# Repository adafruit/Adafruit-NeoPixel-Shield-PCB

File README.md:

## Adafruit NeoPixel Shield for Arduino - 40 RGB LED Pixel Matrix PCB

<a href="http://www.adafruit.com/products/1430"><br/>
Click here to purchase one from the Adafruit shop</a>

PCB files for the Adafruit NeoPixel Shield for Arduino - 40 RGB LED Pixel Matrix. Format is EagleCAD schematic and board layout
* https://www.adafruit.com/product/1430

### Description

Put on your sunglasses before putting this shield onto your 'duino - 40 eye-blistering RGB LEDs adorn the NeoPixel shield for a blast of configurable color. Arranged in a 5x8 matrix, each pixel is individually addressable. Only one pin (Digital #6) is required to control all the LEDs. You can cut a trace and use nearly any other pin if you need some customization.

To make it easy to start, the LEDs are by default powered from the 5V onboard Arduino supply. As long as you aren't lighting up all the pixels full power white that should be fine. If you want to power the shield with an external power supply, solder in the included terminal block (pro-tip: put it on the bottom of the board so it doesn't stick up) to wire in an external 4-6VDC power supply - that power supply will also power the Arduino and shield. If you want to use the terminal block to power the shield but keep the Arduino itself on DC or USB power only, cut the center of the solder jumper to the right of the terminal block. There's a polarity protection FET on the external input in case you wire the power backwards (we would never do that, it was, umm, a friend of ours, yeah that's it!)

If, say, you need MORE blinky, you can chain these together. For the second shield, connect the DIN connection to the first shield's DOUT. Also connect a ground pin together and power with 5V. There you go! You can chain as many as you'd like although after 5 or more shields you may run low on RAM if you're using an UNO.

We include both stacking headers and plain headers. Use whichever you prefer - there isn't a lot of space left over for the 'duino pin breakouts so if you want to wire up some other outputs or sensors the stacking headers are good. For a slim sturdy look, solder on the plain headers.

[Our detailed NeoPixel Uberguide has everything you need to use NeoPixels in any shape and size. Including ready-to-go library & example code for the Arduino UNO/Duemilanove/Diecimila, Flora/Micro/Leonardo, Trinket/Gemma, Arduino Due & Arduino Mega/ADK (all versions)](http://learn.adafruit.com/adafruit-neopixel-uberguide)

**Note**: The terminal blocks included with your product may be blue or black.

### License

Adafruit invests time and resources providing this open source design, please support Adafruit and open-source hardware by purchasing products from [Adafruit](https://www.adafruit.com)!

Designed by Limor Fried/Ladyada for Adafruit Industries.

Creative Commons Attribution/Share-Alike, all text above must be included in any redistribution. See license.txt for additional details.

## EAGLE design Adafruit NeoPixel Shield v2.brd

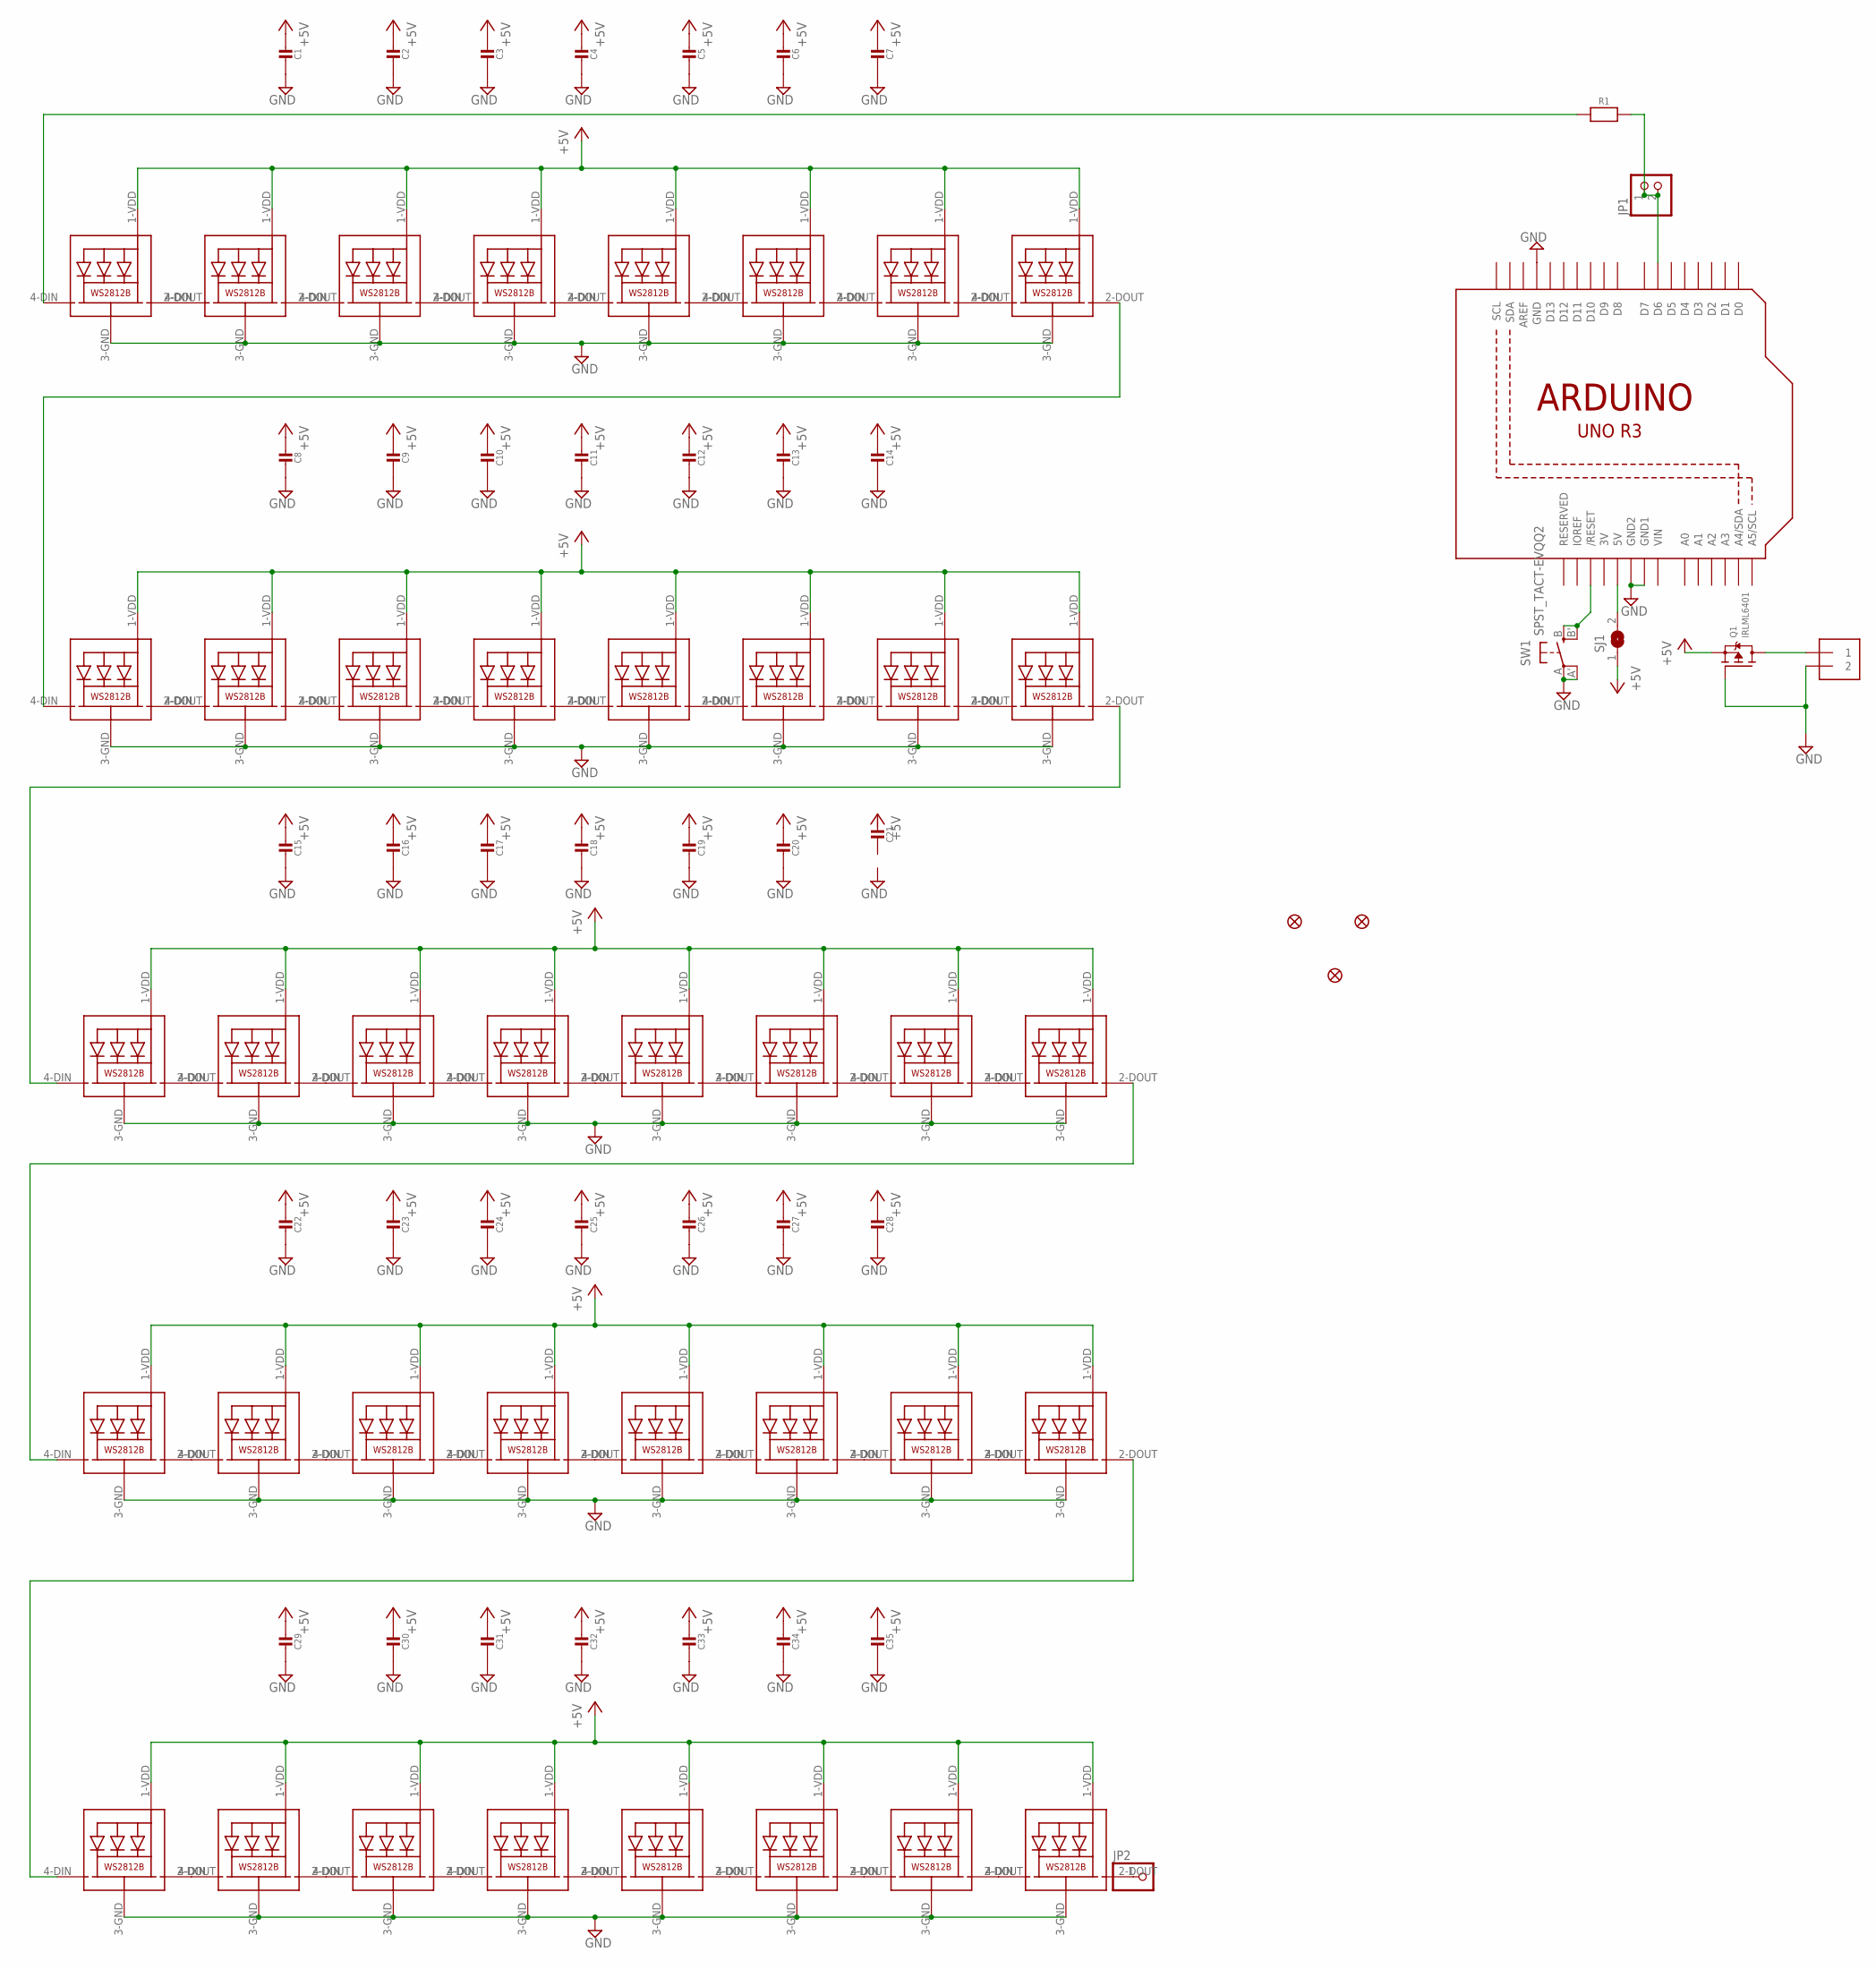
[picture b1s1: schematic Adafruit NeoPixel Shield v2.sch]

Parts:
C1, C2, C3, C4, C5, C6, C7, C8, C9, C10, C11, C12, C13, C14, C15, C16, C17, C18, C19, C20, C21, C22, C23, C24, C25, C26, C27, C28, C29, C30, C31, C32, C33, C34, C35: CAP_CERAMIC_0805NO; _0805NO
FID1, FID2, FID3: FIDUCIAL""; FIDUCIAL_1MM
J1: 1X2-3.5MM
JP1: HEADER-1X2ROUND; 1X02_ROUND
JP2: PINHD-1X1CB; 1X01-CLEANBIG
LED1, LED2, LED3, LED4, LED5, LED6, LED7, LED8, LED9, LED10, LED11, LED12, LED13, LED14, LED15, LED16, LED17, LED18, LED19, LED20, LED21, LED22, LED23, LED24, LED25, LED26, LED27, LED28, LED29, LED30, LED31, LED32, LED33, LED34, LED35, LED36, LED37, LED38, LED39, LED40: WS2812B5050; WS2812B
Q1: IRLML6401; SOT23-WIDE
R1: RESISTOR_0805NO; _0805NO
SJ1: SOLDERJUMPERCLOSED; SOLDERJUMPER_CLOSEDWIRE
SW1: SPST_TACT-EVQQ2; EVQ-Q2
U1: ARDUINOR3-BPLACE

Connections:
3V: U1.3V
+5V: C1.1, C2.1, C3.1, C4.1, C5.1, C6.1, C7.1, C8.1, C9.1, C10.1, C11.1, C12.1, C13.1, C14.1, C15.1, C16.1, C17.1, C18.1, C19.1, C20.1, C21.1, C22.1, C23.1, C24.1, C25.1, C26.1, C27.1, C28.1, C29.1, C30.1, C31.1, C32.1, C33.1, C34.1, C35.1, LED1.1-VDD (VDD), LED2.1-VDD (VDD), LED3.1-VDD (VDD), LED4.1-VDD (VDD), LED5.1-VDD (VDD), LED6.1-VDD (VDD), LED7.1-VDD (VDD), LED8.1-VDD (VDD), LED9.1-VDD (VDD), LED10.1-VDD (VDD), LED11.1-VDD (VDD), LED12.1-VDD (VDD), LED13.1-VDD (VDD), LED14.1-VDD (VDD), LED15.1-VDD (VDD), LED16.1-VDD (VDD), LED17.1-VDD (VDD), LED18.1-VDD (VDD), LED19.1-VDD (VDD), LED20.1-VDD (VDD), LED21.1-VDD (VDD), LED22.1-VDD (VDD), LED23.1-VDD (VDD), LED24.1-VDD (VDD), LED25.1-VDD (VDD), LED26.1-VDD (VDD), LED27.1-VDD (VDD), LED28.1-VDD (VDD), LED29.1-VDD (VDD), LED30.1-VDD (VDD), LED31.1-VDD (VDD), LED32.1-VDD (VDD), LED33.1-VDD (VDD), LED34.1-VDD (VDD), LED35.1-VDD (VDD), LED36.1-VDD (VDD), LED37.1-VDD (VDD), LED38.1-VDD (VDD), LED39.1-VDD (VDD), LED40.1-VDD (VDD), Q1.2 (S), SJ1.1
GND: C1.2, C2.2, C3.2, C4.2, C5.2, C6.2, C7.2, C8.2, C9.2, C10.2, C11.2, C12.2, C13.2, C14.2, C15.2, C16.2, C17.2, C18.2, C19.2, C20.2, C21.2, C22.2, C23.2, C24.2, C25.2, C26.2, C27.2, C28.2, C29.2, C30.2, C31.2, C32.2, C33.2, C34.2, C35.2, J1.2, LED1.3-GND (GND), LED2.3-GND (GND), LED3.3-GND (GND), LED4.3-GND (GND), LED5.3-GND (GND), LED6.3-GND (GND), LED7.3-GND (GND), LED8.3-GND (GND), LED9.3-GND (GND), LED10.3-GND (GND), LED11.3-GND (GND), LED12.3-GND (GND), LED13.3-GND (GND), LED14.3-GND (GND), LED15.3-GND (GND), LED16.3-GND (GND), LED17.3-GND (GND), LED18.3-GND (GND), LED19.3-GND (GND), LED20.3-GND (GND), LED21.3-GND (GND), LED22.3-GND (GND), LED23.3-GND (GND), LED24.3-GND (GND), LED25.3-GND (GND), LED26.3-GND (GND), LED27.3-GND (GND), LED28.3-GND (GND), LED29.3-GND (GND), LED30.3-GND (GND), LED31.3-GND (GND), LED32.3-GND (GND), LED33.3-GND (GND), LED34.3-GND (GND), LED35.3-GND (GND), LED36.3-GND (GND), LED37.3-GND (GND), LED38.3-GND (GND), LED39.3-GND (GND), LED40.3-GND (GND), Q1.1 (G), SW1.A, SW1.A' (P1), U1.GND, U1.GND1, U1.GND2
unnamed: LED1.2-DOUT (DO), LED2.4-DIN (DI)
unnamed: LED2.2-DOUT (DO), LED3.4-DIN (DI)
unnamed: LED3.2-DOUT (DO), LED4.4-DIN (DI)
unnamed: LED4.2-DOUT (DO), LED5.4-DIN (DI)
unnamed: LED5.2-DOUT (DO), LED6.4-DIN (DI)
unnamed: LED6.2-DOUT (DO), LED7.4-DIN (DI)
unnamed: LED7.2-DOUT (DO), LED8.4-DIN (DI)
unnamed: LED9.2-DOUT (DO), LED10.4-DIN (DI)
unnamed: LED10.2-DOUT (DO), LED11.4-DIN (DI)
unnamed: LED11.2-DOUT (DO), LED12.4-DIN (DI)
unnamed: LED12.2-DOUT (DO), LED13.4-DIN (DI)
unnamed: LED13.2-DOUT (DO), LED14.4-DIN (DI)
unnamed: LED14.2-DOUT (DO), LED15.4-DIN (DI)
unnamed: LED15.2-DOUT (DO), LED16.4-DIN (DI)
unnamed: LED8.2-DOUT (DO), LED9.4-DIN (DI)
unnamed: LED17.2-DOUT (DO), LED18.4-DIN (DI)
unnamed: LED18.2-DOUT (DO), LED19.4-DIN (DI)
unnamed: LED19.2-DOUT (DO), LED20.4-DIN (DI)
unnamed: LED20.2-DOUT (DO), LED21.4-DIN (DI)
unnamed: LED21.2-DOUT (DO), LED22.4-DIN (DI)
unnamed: LED22.2-DOUT (DO), LED23.4-DIN (DI)
unnamed: LED23.2-DOUT (DO), LED24.4-DIN (DI)
unnamed: LED16.2-DOUT (DO), LED17.4-DIN (DI)
unnamed: LED25.2-DOUT (DO), LED26.4-DIN (DI)
unnamed: LED26.2-DOUT (DO), LED27.4-DIN (DI)
unnamed: LED27.2-DOUT (DO), LED28.4-DIN (DI)
unnamed: LED28.2-DOUT (DO), LED29.4-DIN (DI)
unnamed: LED29.2-DOUT (DO), LED30.4-DIN (DI)
unnamed: LED30.2-DOUT (DO), LED31.4-DIN (DI)
unnamed: LED31.2-DOUT (DO), LED32.4-DIN (DI)
unnamed: LED24.2-DOUT (DO), LED25.4-DIN (DI)
unnamed: LED33.2-DOUT (DO), LED34.4-DIN (DI)
unnamed: LED34.2-DOUT (DO), LED35.4-DIN (DI)
unnamed: LED35.2-DOUT (DO), LED36.4-DIN (DI)
unnamed: LED36.2-DOUT (DO), LED37.4-DIN (DI)
unnamed: LED37.2-DOUT (DO), LED38.4-DIN (DI)
unnamed: LED38.2-DOUT (DO), LED39.4-DIN (DI)
unnamed: LED39.2-DOUT (DO), LED40.4-DIN (DI)
unnamed: LED32.2-DOUT (DO), LED33.4-DIN (DI)
unnamed: SW1.B (S), SW1.B' (S1), U1.RESET (/RESET)
unnamed: SJ1.2, U1.5V
unnamed: JP2.1, LED40.2-DOUT (DO)
unnamed: LED1.4-DIN (DI), R1.1
unnamed: JP1.1, JP1.2, R1.2, U1.D6
PWRIN: J1.1, Q1.3 (D)
VIN: U1.VIN

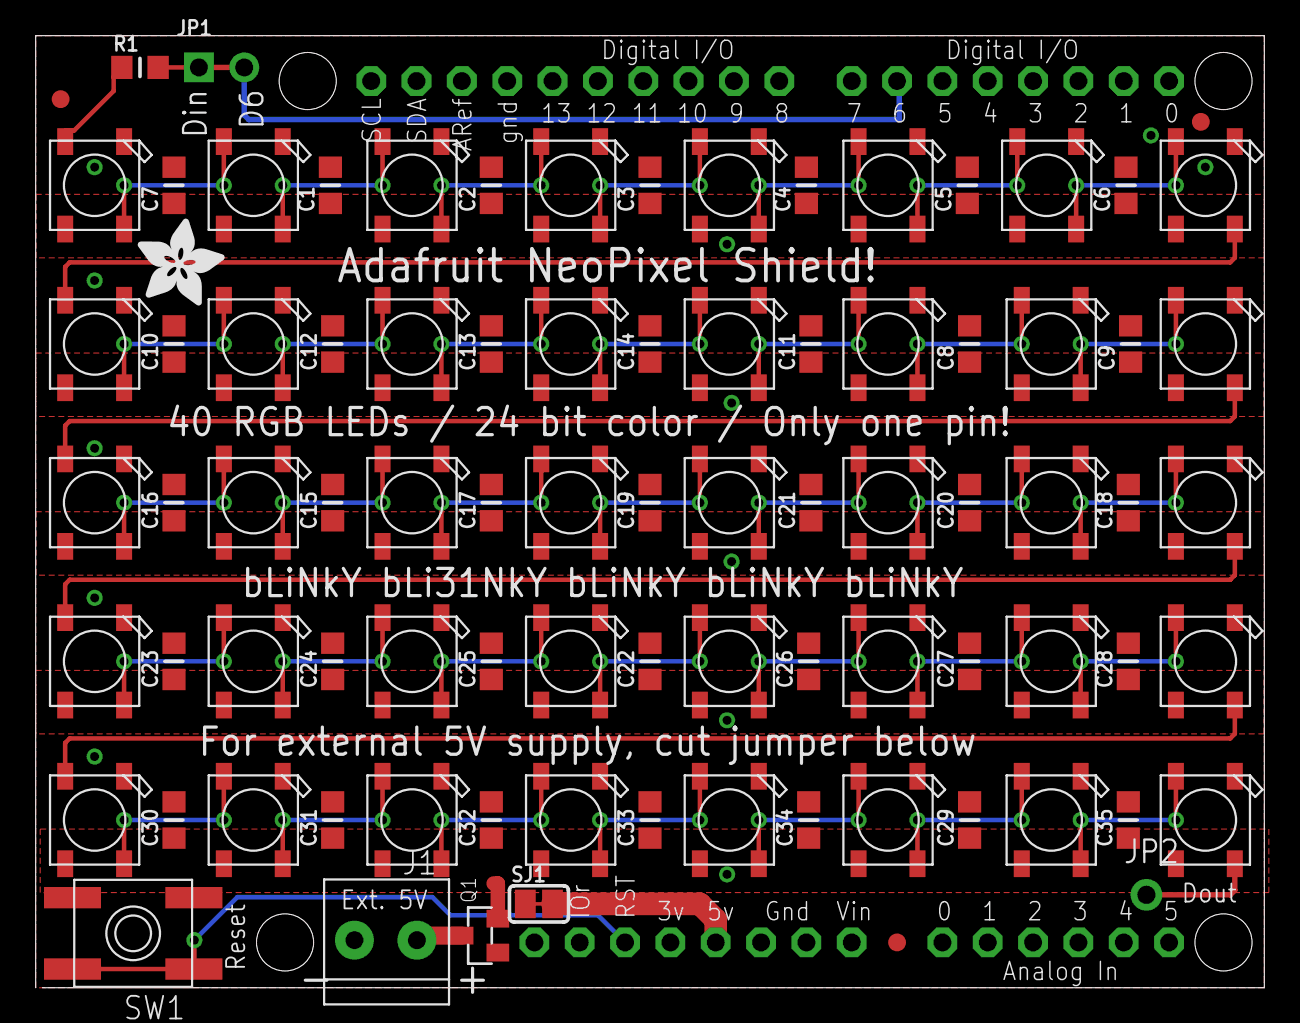
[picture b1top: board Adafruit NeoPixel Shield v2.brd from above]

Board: 2 copper layers, 68.8 x 53.3 mm, 88 parts (1 on the bottom side), 47 nets.

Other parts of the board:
U$1: ADAFRUIT_5MM
U$2: ADAFRUIT_TEXT_30MM

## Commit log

2014-03-03 woo files!
2014-03-03 read
2019-02-10 Create Zionism
2019-02-10 Create Universal ink
2019-02-10 Create 5x8 zionism
2019-02-10 Create Install html super glue
2019-02-10 Create Oscarg933
2019-02-10 Create Hacker-storm-spray
2019-07-17 updated to use cookiecutter for pcb repos

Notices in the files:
parts and their libraries:
microbuilder: This work is placed in the public domain, and may be freely used for commercial and non-commercial work with the following conditions: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
